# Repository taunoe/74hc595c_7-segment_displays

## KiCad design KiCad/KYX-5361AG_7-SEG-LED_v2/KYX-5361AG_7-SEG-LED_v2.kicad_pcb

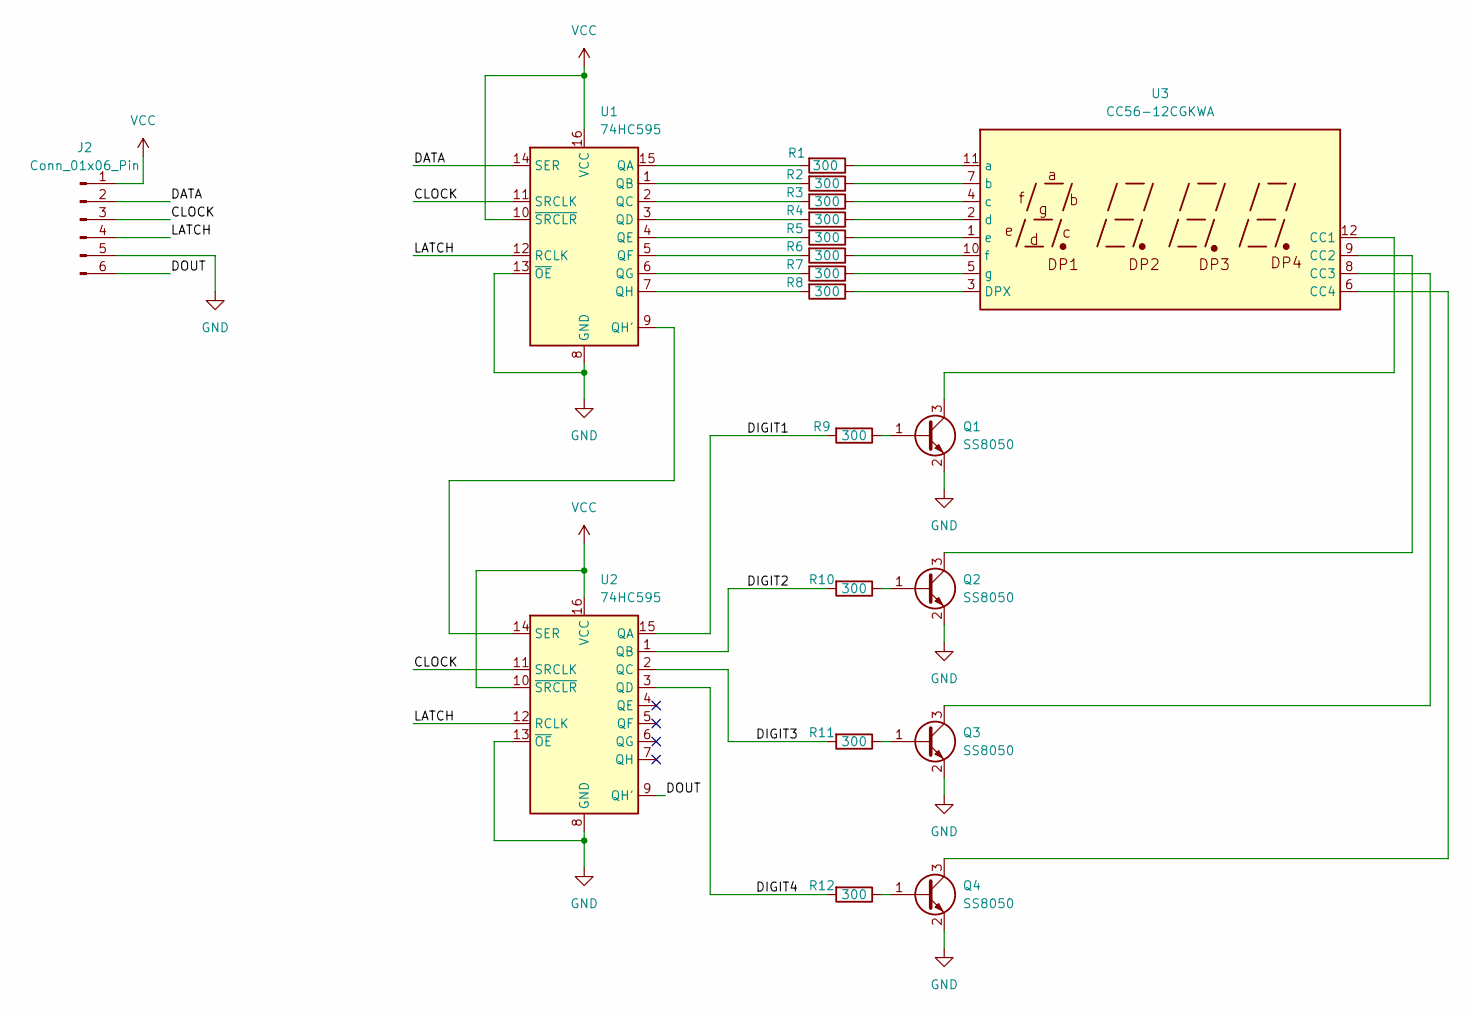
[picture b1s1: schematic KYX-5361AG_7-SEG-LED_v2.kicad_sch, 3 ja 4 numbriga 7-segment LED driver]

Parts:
J2: Conn_01x06_Pin; PinHeader_1x06_P2.54mm_Vertical
Q1, Q2, Q3, Q4: SS8050; SOT-23
R1, R2, R3, R4, R5, R6, R7, R8, R9, R10, R11, R12: 300; R_1206_3216Metric_Pad1.30x1.75mm_HandSolder
U1, U2: 74HC595; SOIC-16_3.9x9.9mm_P1.27mm
U3: CC56-12CGKWA; CA56-12CGKWA

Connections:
/CLOCK: J2.3, U1.11 (SRCLK), U2.11 (SRCLK)
/DATA: J2.2, U1.14 (SER)
/DIGIT1: R9.2, U2.15 (QA)
/DIGIT2: R10.2, U2.1 (QB)
/DIGIT3: R11.2, U2.2 (QC)
/DIGIT4: R12.2, U2.3 (QD)
/DOUT: J2.6, U2.9 (QH')
/LATCH: J2.4, U1.12 (RCLK), U2.12 (RCLK)
GND: J2.5, Q1.2 (E), Q2.2 (E), Q3.2 (E), Q4.2 (E), U1.8 (GND), U1.13 (~OE), U2.8 (GND), U2.13 (~OE)
unnamed: Q1.1 (B), R9.1
unnamed: Q1.3 (C), U3.12 (CC1)
unnamed: Q2.1 (B), R10.1
unnamed: Q2.3 (C), U3.9 (CC2)
unnamed: Q3.1 (B), R11.1
unnamed: Q3.3 (C), U3.8 (CC3)
unnamed: Q4.1 (B), R12.1
unnamed: Q4.3 (C), U3.6 (CC4)
unnamed: R1.2, U1.15 (QA)
unnamed: R2.2, U1.1 (QB)
unnamed: R3.2, U1.2 (QC)
unnamed: R4.2, U1.3 (QD)
unnamed: R5.2, U1.4 (QE)
unnamed: R6.2, U1.5 (QF)
unnamed: R7.2, U1.6 (QG)
unnamed: U1.9 (QH'), U2.14 (SER)
unnamed: R8.2, U1.7 (QH)
unnamed: R8.1, U3.3 (DPX)
unnamed: R1.1, U3.11 (a)
unnamed: R2.1, U3.7 (b)
unnamed: R3.1, U3.4 (c)
unnamed: R4.1, U3.2 (d)
unnamed: R5.1, U3.1 (e)
unnamed: R6.1, U3.10 (f)
unnamed: R7.1, U3.5 (g)
VCC: J2.1, U1.10 (~SRCLR), U1.16 (VCC), U2.10 (~SRCLR), U2.16 (VCC)

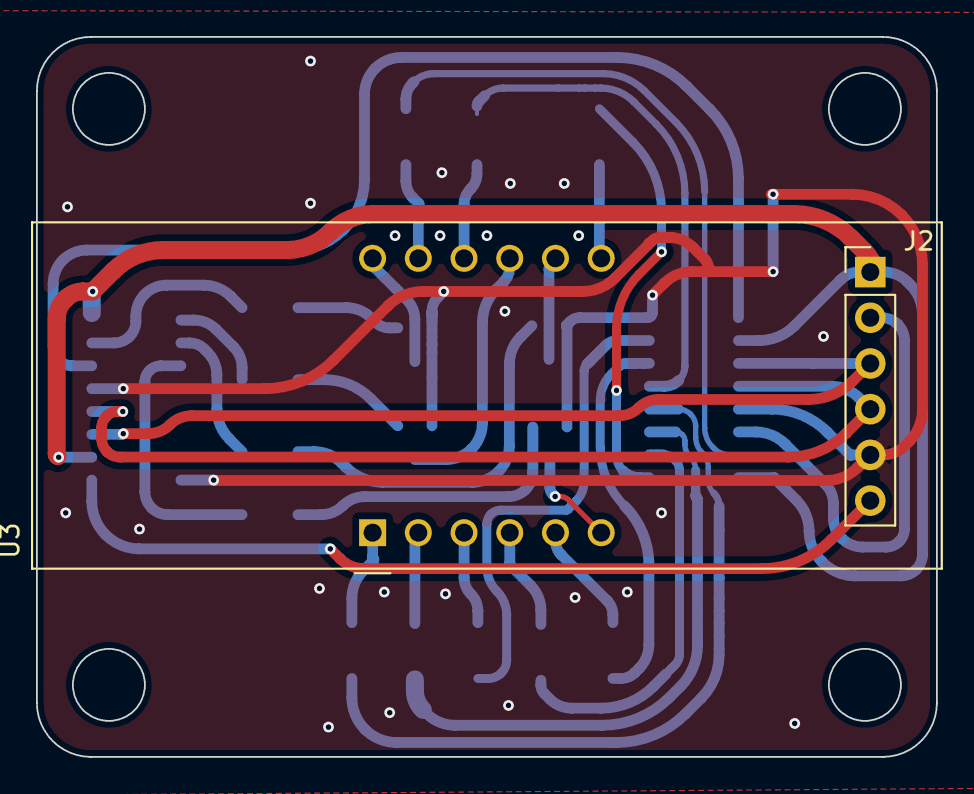
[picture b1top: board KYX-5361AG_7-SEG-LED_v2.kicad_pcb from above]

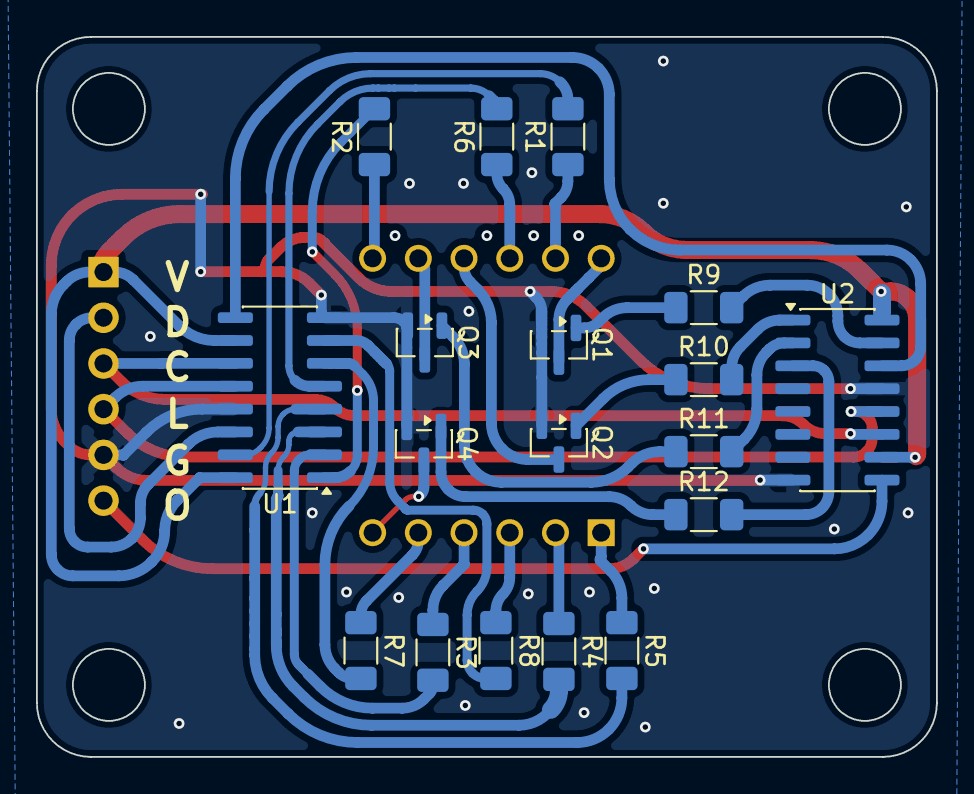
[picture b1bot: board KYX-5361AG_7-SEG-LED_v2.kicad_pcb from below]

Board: 2 copper layers, 50.0 x 40.0 mm, 20 parts (18 on the bottom side), 35 nets.

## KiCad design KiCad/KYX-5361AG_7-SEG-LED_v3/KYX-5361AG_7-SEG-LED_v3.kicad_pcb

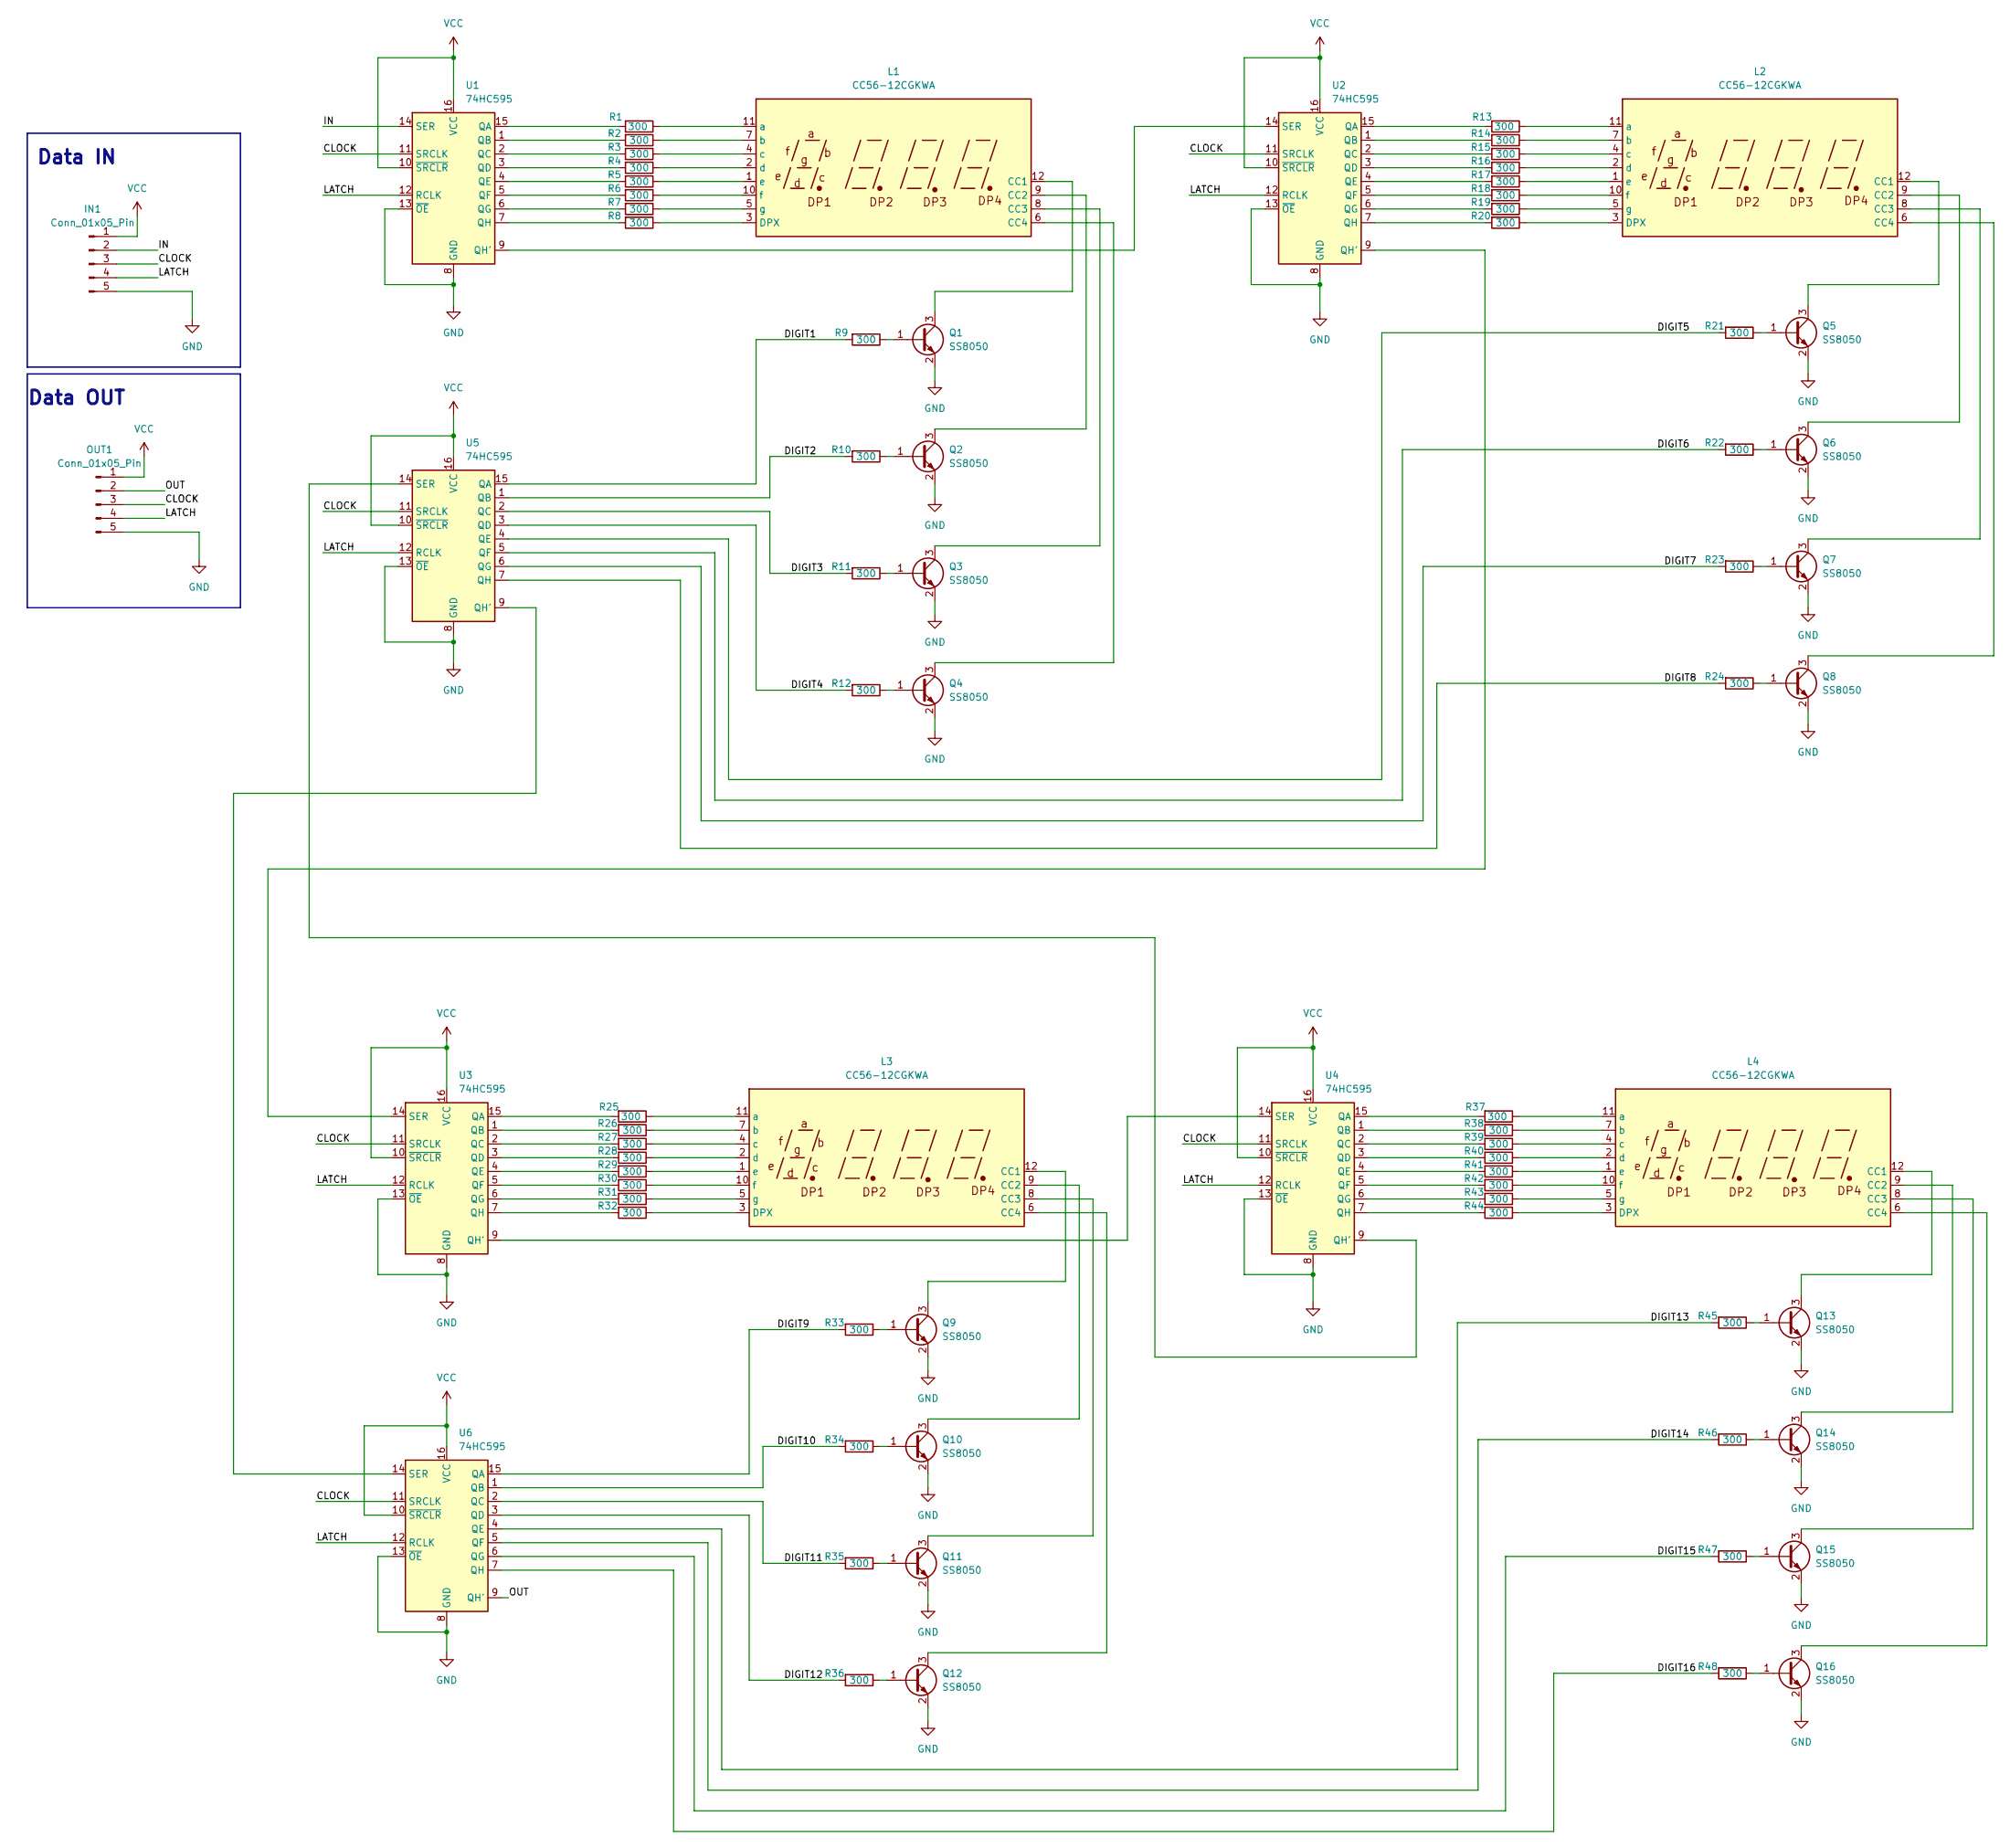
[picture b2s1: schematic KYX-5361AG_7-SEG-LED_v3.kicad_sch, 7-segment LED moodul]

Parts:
IN1: Conn_01x05_Pin; PinSocket_1x05_P2.54mm_Vertical
L1, L2, L3, L4: CC56-12CGKWA; CA56-12CGKWA
OUT1: Conn_01x05_Pin; PinSocket_1x05_P2.54mm_Vertical
Q1, Q2, Q3, Q4, Q5, Q6, Q7, Q8, Q9, Q10, Q11, Q12, Q13, Q14, Q15, Q16: SS8050; SOT-23
R1, R2, R3, R4, R5, R6, R7, R8, R9, R10, R11, R12, R13, R14, R15, R16, R17, R18, R19, R20, R21, R22, R23, R24, R25, R26, R27, R28, R29, R30, R31, R32, R33, R34, R35, R36, R37, R38, R39, R40, R41, R42, R43, R44, R45, R46, R47, R48: 300; R_0805_2012Metric_Pad1.20x1.40mm_HandSolder
U1, U2, U3, U4, U5, U6: 74HC595; SOIC-16_3.9x9.9mm_P1.27mm

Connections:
/CLOCK: IN1.3, OUT1.3, U1.11 (SRCLK), U2.11 (SRCLK), U3.11 (SRCLK), U4.11 (SRCLK), U5.11 (SRCLK), U6.11 (SRCLK)
/DIGIT1: R9.2, U5.15 (QA)
/DIGIT2: R10.2, U5.1 (QB)
/DIGIT3: R11.2, U5.2 (QC)
/DIGIT4: R12.2, U5.3 (QD)
/DIGIT5: R21.2, U5.4 (QE)
/DIGIT6: R22.2, U5.5 (QF)
/DIGIT7: R23.2, U5.6 (QG)
/DIGIT8: R24.2, U5.7 (QH)
/DIGIT9: R33.2, U6.15 (QA)
/DIGIT10: R34.2, U6.1 (QB)
/DIGIT11: R35.2, U6.2 (QC)
/DIGIT12: R36.2, U6.3 (QD)
/DIGIT13: R45.2, U6.4 (QE)
/DIGIT14: R46.2, U6.5 (QF)
/DIGIT15: R47.2, U6.6 (QG)
/DIGIT16: R48.2, U6.7 (QH)
/IN: IN1.2, U1.14 (SER)
/LATCH: IN1.4, OUT1.4, U1.12 (RCLK), U2.12 (RCLK), U3.12 (RCLK), U4.12 (RCLK), U5.12 (RCLK), U6.12 (RCLK)
/OUT: OUT1.2, U6.9 (QH')
GND: IN1.5, OUT1.5, Q1.2 (E), Q2.2 (E), Q3.2 (E), Q4.2 (E), Q5.2 (E), Q6.2 (E), Q7.2 (E), Q8.2 (E), Q9.2 (E), Q10.2 (E), Q11.2 (E), Q12.2 (E), Q13.2 (E), Q14.2 (E), Q15.2 (E), Q16.2 (E), U1.8 (GND), U1.13 (~OE), U2.8 (GND), U2.13 (~OE), U3.8 (GND), U3.13 (~OE), U4.8 (GND), U4.13 (~OE), U5.8 (GND), U5.13 (~OE), U6.8 (GND), U6.13 (~OE)
unnamed: L1.12 (CC1), Q1.3 (C)
unnamed: L1.9 (CC2), Q2.3 (C)
unnamed: L1.8 (CC3), Q3.3 (C)
unnamed: L1.6 (CC4), Q4.3 (C)
unnamed: L1.3 (DPX), R8.1
unnamed: L1.11 (a), R1.1
unnamed: L1.7 (b), R2.1
unnamed: L1.4 (c), R3.1
unnamed: L1.2 (d), R4.1
unnamed: L1.1 (e), R5.1
unnamed: L1.10 (f), R6.1
unnamed: L1.5 (g), R7.1
unnamed: L2.12 (CC1), Q5.3 (C)
unnamed: L2.9 (CC2), Q6.3 (C)
unnamed: L2.8 (CC3), Q7.3 (C)
unnamed: L2.6 (CC4), Q8.3 (C)
unnamed: L2.3 (DPX), R20.1
unnamed: L2.11 (a), R13.1
unnamed: L2.7 (b), R14.1
unnamed: L2.4 (c), R15.1
unnamed: L2.2 (d), R16.1
unnamed: L2.1 (e), R17.1
unnamed: L2.10 (f), R18.1
unnamed: L2.5 (g), R19.1
unnamed: L3.12 (CC1), Q9.3 (C)
unnamed: L3.9 (CC2), Q10.3 (C)
unnamed: L3.8 (CC3), Q11.3 (C)
unnamed: L3.6 (CC4), Q12.3 (C)
unnamed: L3.3 (DPX), R32.1
unnamed: L3.11 (a), R25.1
unnamed: L3.7 (b), R26.1
unnamed: L3.4 (c), R27.1
unnamed: L3.2 (d), R28.1
unnamed: L3.1 (e), R29.1
unnamed: L3.10 (f), R30.1
unnamed: L3.5 (g), R31.1
unnamed: L4.12 (CC1), Q13.3 (C)
unnamed: L4.9 (CC2), Q14.3 (C)
unnamed: L4.8 (CC3), Q15.3 (C)
unnamed: L4.6 (CC4), Q16.3 (C)
unnamed: L4.3 (DPX), R44.1
unnamed: L4.11 (a), R37.1
unnamed: L4.7 (b), R38.1
unnamed: L4.4 (c), R39.1
unnamed: L4.2 (d), R40.1
unnamed: L4.1 (e), R41.1
unnamed: L4.10 (f), R42.1
unnamed: L4.5 (g), R43.1
unnamed: Q1.1 (B), R9.1
unnamed: Q2.1 (B), R10.1
unnamed: Q3.1 (B), R11.1
unnamed: Q4.1 (B), R12.1
unnamed: Q5.1 (B), R21.1
unnamed: Q6.1 (B), R22.1
unnamed: Q7.1 (B), R23.1
unnamed: Q8.1 (B), R24.1
unnamed: Q9.1 (B), R33.1
unnamed: Q10.1 (B), R34.1
unnamed: Q11.1 (B), R35.1
unnamed: Q12.1 (B), R36.1
unnamed: Q13.1 (B), R45.1
unnamed: Q14.1 (B), R46.1
unnamed: Q15.1 (B), R47.1
unnamed: Q16.1 (B), R48.1
unnamed: R1.2, U1.15 (QA)
unnamed: R2.2, U1.1 (QB)
unnamed: R3.2, U1.2 (QC)
unnamed: R4.2, U1.3 (QD)
unnamed: R5.2, U1.4 (QE)
unnamed: R6.2, U1.5 (QF)
unnamed: R7.2, U1.6 (QG)
unnamed: U1.9 (QH'), U2.14 (SER)
unnamed: R8.2, U1.7 (QH)
unnamed: R13.2, U2.15 (QA)
unnamed: R14.2, U2.1 (QB)
unnamed: R15.2, U2.2 (QC)
unnamed: R16.2, U2.3 (QD)
unnamed: R17.2, U2.4 (QE)
unnamed: R18.2, U2.5 (QF)
unnamed: R19.2, U2.6 (QG)
unnamed: U2.9 (QH'), U3.14 (SER)
unnamed: R20.2, U2.7 (QH)
unnamed: R25.2, U3.15 (QA)
unnamed: R26.2, U3.1 (QB)
unnamed: R27.2, U3.2 (QC)
unnamed: R28.2, U3.3 (QD)
unnamed: R29.2, U3.4 (QE)
unnamed: R30.2, U3.5 (QF)
unnamed: R31.2, U3.6 (QG)
unnamed: U3.9 (QH'), U4.14 (SER)
unnamed: R32.2, U3.7 (QH)
unnamed: R37.2, U4.15 (QA)
unnamed: R38.2, U4.1 (QB)
unnamed: R39.2, U4.2 (QC)
unnamed: R40.2, U4.3 (QD)
unnamed: R41.2, U4.4 (QE)
unnamed: R42.2, U4.5 (QF)
unnamed: R43.2, U4.6 (QG)
unnamed: U4.9 (QH'), U5.14 (SER)
unnamed: R44.2, U4.7 (QH)
unnamed: U5.9 (QH'), U6.14 (SER)
VCC: IN1.1, OUT1.1, U1.10 (~SRCLR), U1.16 (VCC), U2.10 (~SRCLR), U2.16 (VCC), U3.10 (~SRCLR), U3.16 (VCC), U4.10 (~SRCLR), U4.16 (VCC), U5.10 (~SRCLR), U5.16 (VCC), U6.10 (~SRCLR), U6.16 (VCC)

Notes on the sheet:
Data IN
Data OUT

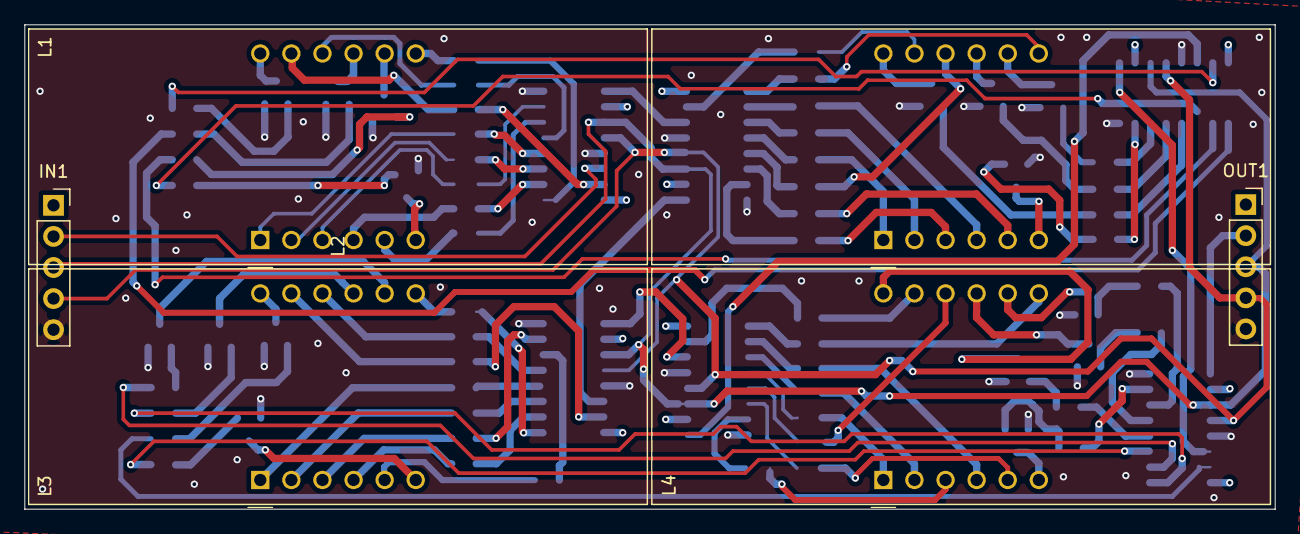
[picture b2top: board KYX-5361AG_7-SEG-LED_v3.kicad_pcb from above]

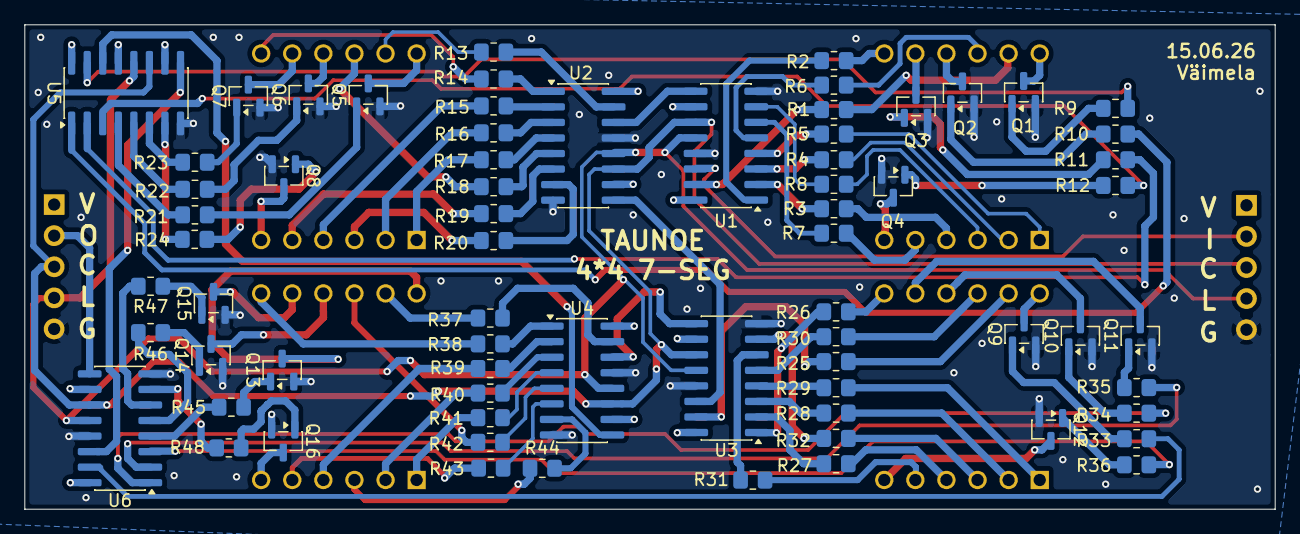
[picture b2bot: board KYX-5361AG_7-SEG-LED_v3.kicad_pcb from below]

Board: 4 copper layers, 102.1 x 39.6 mm, 76 parts (70 on the bottom side), 123 nets.

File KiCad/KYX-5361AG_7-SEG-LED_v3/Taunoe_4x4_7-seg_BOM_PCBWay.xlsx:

|  |  | xxxx xxxx xxxxx xxPCS BOM (Sample Bill of Materials)
Item # | *Designator | *Qty | Manufacturer | *Mfg Part # | Description / Value | *Package/Footprint | Type | Your Instructions / Notes
1 | Q1, Q2, Q3, Q4, Q5, Q6, Q7, Q8, Q9, Q10, Q11, Q12, Q13, Q14, Q15, Q16 | 16 | JSMSEMI | SS8050 | SS8050, SOT-23 | SOT-23 | SMD
2 | R1, R2, R3, R4, R5, R6, R7, R8, R9, R10, R11, R12, R13, R14, R15, R16, R17, R18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 | 48 | YAGEO | RC0805FR-07300RL | RES 300Ω ±1% 125mW 0805 | 805 | SMD
3 | U1, U2, U3, U4, U5, U6 | 6 | GR | 74HC595 | 74HC595, SOIC-16_3.9x9.9mm_P1.27mm | SOP-16 | SMD
4 | IN1, OUT1 | 2 | - | - | - | - | - | The customer installs.
5 | L1, L2, L3, L4 | 4 | - | - | - | - | - | The customer installs.
